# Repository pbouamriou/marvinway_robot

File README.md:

# marvinway
Source du projet Marvin Way (le segway depressif O_o)

## Arborescence ##

### brain ###

Projet de la carte de contrôle Haut niveau de Marvin

### control

Projet pour la carte de contrôle des moteurs

### docs

Contient la documentation globale du projet

### experience

Contient les exemples des expériences associés au projet marvinway

### meca

Contient la conception mecanique de Marvin

### shield

Projet permettant la communication entre le Brain et le reste du monde (la moelle epinière en soit)

### supply

Projet de gestion de l'alimentation

### utils

Contient des librairies utils ou des ensembles de configurations

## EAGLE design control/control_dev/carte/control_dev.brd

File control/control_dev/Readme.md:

# Carte de développement pour le pilotage des moteurs

## Configuration

Vous devez suivre la procédure de configuration d'EAGLE décrite dans le README situé dans utils/Eagle 

Pour ajouter le projet dans Eagle :

- Aller dans le `Control Panel -> Directories`

- Dans le cinquième champs `Projects` ajouter le répertoire correspondant au répertoire parent du répertoire carte

## Sources

[add custom project folder into eagle]: http://fsdportal.com/add-custom-project-folder-eagle-control-panel/	"add custom project folder into eagle"

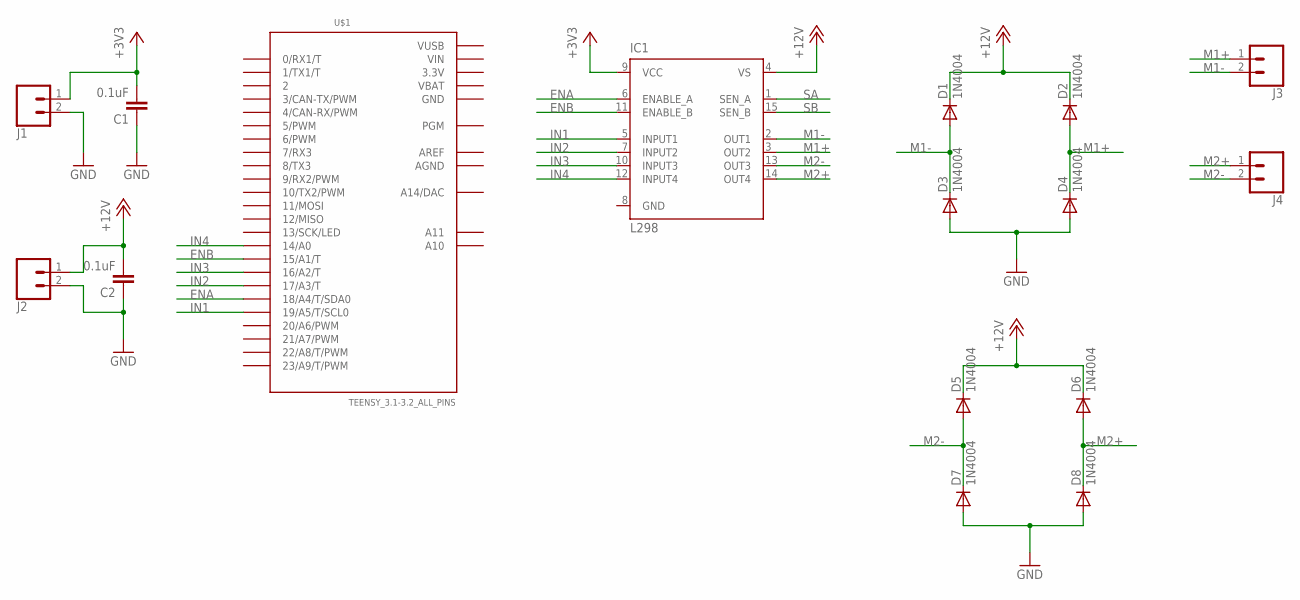
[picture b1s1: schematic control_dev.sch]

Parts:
C1, C2: 0.1uF; CAP-PTH-SMALL-KIT
D1, D2, D3, D4, D5, D6, D7, D8: 1N4004; DO41-10
IC1: L298; MULTIWATT-15
J1, J2, J3, J4: CONN_023.5MM; SCREWTERMINAL-3.5MM-2
U$1: TEENSY_3.1-3.2_ALL_PINS; TEENSY_3.0-3.2&LC_ALL_PINS

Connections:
3.3V: U$1.3.3V, U$1.3.3V1 (3.3V)
+3V3: C1.2, IC1.9 (VCC), J1.1
+12V: C2.2, D1.C, D2.C, D5.C, D6.C, IC1.4 (VS), J2.1
AGND: U$1.AGND
AREF: U$1.AREF
ENA: IC1.6 (ENABLE_A), U$1.18/A4 (18/A4/T/SDA0)
ENB: IC1.11 (ENABLE_B), U$1.15/A1 (15/A1/T)
GND: C1.1, C2.1, D3.A, D4.A, D7.A, D8.A, IC1.8 (GND), J1.2, J2.2, U$1.GND, U$1.GND1 (GND)
IN1: IC1.5 (INPUT1), U$1.19/A5 (19/A5/T/SCL0)
IN2: IC1.7 (INPUT2), U$1.17/A3 (17/A3/T)
IN3: IC1.10 (INPUT3), U$1.16/A2 (16/A2/T)
IN4: IC1.12 (INPUT4), U$1.14/A0
M1+: D2.A, D4.C, IC1.3 (OUT2), J3.1
M1-: D1.A, D3.C, IC1.2 (OUT1), J3.2
M2+: D6.A, D8.C, IC1.14 (OUT4), J4.1
M2-: D5.A, D7.C, IC1.13 (OUT3), J4.2
SA: IC1.1 (SEN_A)
SB: IC1.15 (SEN_B)
VBAT: U$1.VBAT
VIN: U$1.VIN
VUSB: U$1.VUSB

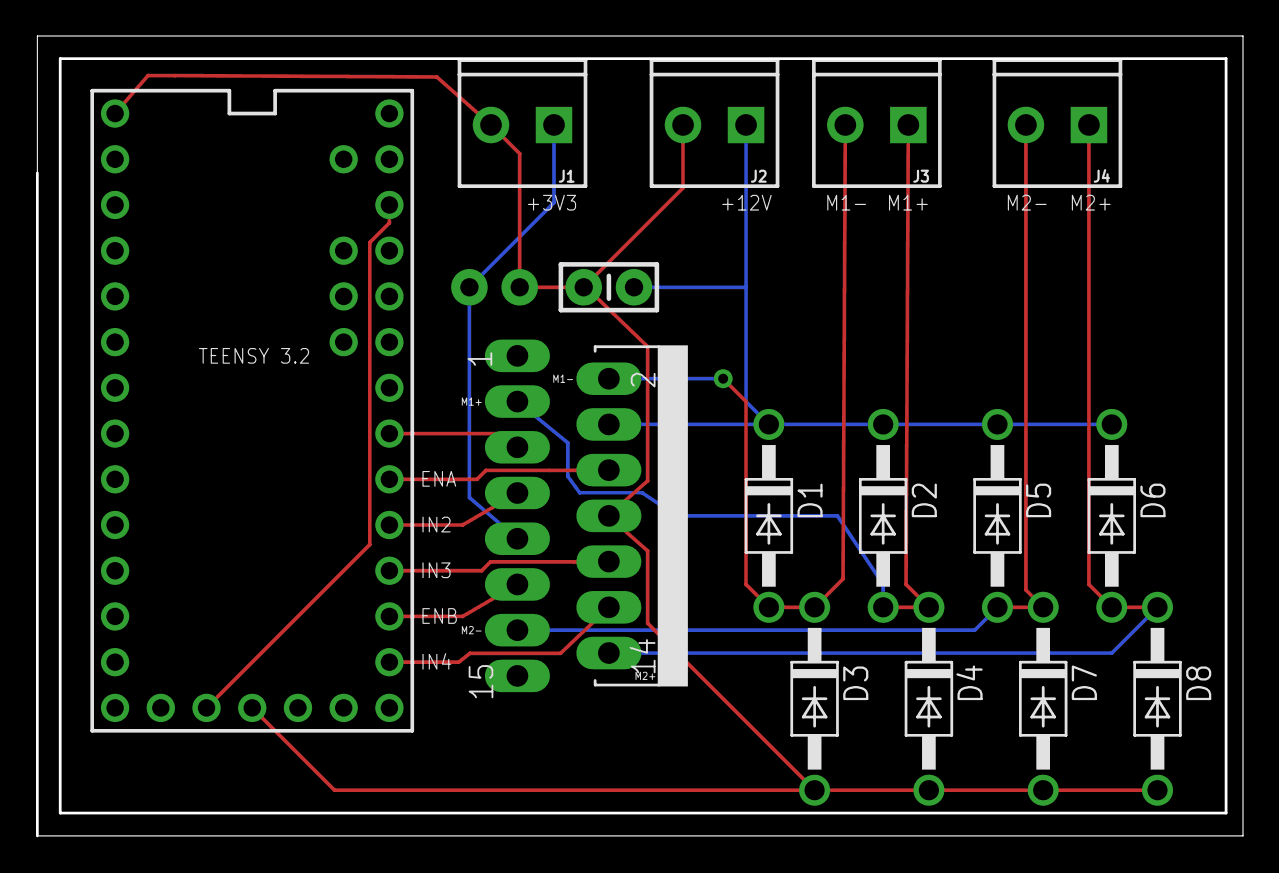
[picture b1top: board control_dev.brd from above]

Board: 2 copper layers, 66.9 x 44.4 mm, 16 parts (1 on the bottom side), 14 nets.

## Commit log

2016-01-30 ajout des pieces solidwors
2016-01-30 conception mecanique de marvin 1
2016-02-18 ajout de marvin
2016-02-22 ajout de la tete de marvin sous solidworks
2016-02-25 Ajout d'un programme de test qui est produit grace a CMAKE.
2016-02-25 Enrichissement du README.md pour ajouter des explications sur l'installation de l'environement.
2016-03-02 Ajout de nouveaux tests + correction cmake (upload et librairies).
2016-03-02 Maj de la documentation par rapport à cmake et l'upload.
2016-03-06 ajout du fichier tex décrivant les besoins de Marvin
2016-03-07 ajout du cours d'élec basé sur les vidéos de Thonain
2016-03-07 correction comprenant pour que les références vers la courbe se fassent correctement
2016-03-16 Ajout du programme de pilotage du potentiometre numerique.
2016-04-19 Ajout d'un test de pwm avec écran LCD.
2016-04-26 Ajout de CMake pour latex
2016-05-03 Ajout d'un programme qui augmente et diminue automatiquement une pwm sur la pin 3 de la teensy pour ajuster la vitesse du moteur sur un circuit de puissance
2016-05-03 Ajustement de Arduino.cmake pour qu'il utilise teensy_loader_cli au lieu de teensy pour déployer sur la teensy directement
2016-05-03 ajout du script d'installation teensy_loader_cli pour la compatibilité avec le nouveau build cmake
2016-05-03 Ajout d'un paragraphe de description pour installation de la commande teensy_loader_cli
2016-05-17 Ajout doc (partiel) sur le driver de mofset.
2016-05-17 Mise a jour de la documentation pour les transistors MOFSET
2016-05-17 Ajout d'une regle pour gitignore
2016-05-31 Ajout de quelques chapitre à compléter et mise à jour du CMake pour la gestion de bibtex
2016-07-06 Ajout d'un programme de visualisation gyroscopic OpenGL
2016-08-09 application OpenGL pour observer le comportement du capteur IMU5066
2016-08-09 Ajout d'une cheat sheet for vim
2016-08-09 Ajout des librairie d'utilisation du MPU6050 compilé avec cmake
2016-08-09 ajout du fichier bibtex pour la bibliographie
2016-08-09 renommage de setup en configure
2016-08-09 ajout du dépot de gestion des ports series
2016-08-09 mise à jour de configure
2016-08-09 Ajout du sous module pour les ports séries
2016-08-10 modification des valeurs offset initiales du gyroscrope Ajout d'un README.md pour utiliser le gyroscope Modification du dépot serial pour une integration plus facile
2016-08-10 Ajout du svg teensy
2016-08-10 Ajout du svg dans le markdown
2016-08-10 Correction ajout svg dans markdown
2016-08-10 correction README
2016-08-10 Tentative d'affichage d'une icone en png dans le markdown
2016-12-20 Mise en gconf de la partie vhdl
2016-12-20 Ajout de l'environement de test.
2016-12-20 Correctionde l'environement de simulation du decodeur
2017-01-16 Ajout du code vhdl qui fait la gestion memeoire des servomoteur + script
2017-01-31 Ajout du module servomoteur, avec l environement de simultation associé
2017-01-31 Ajout du dirvers avec des consignes en angle de 0 a 180 deg
2017-01-31 Ajout du module en charge des IO
2017-02-28 debug du module inputoutput
2017-03-28 Ajout de la datasheet du composant ADC sur 12bit, avec 8 channels
2017-05-01 Version initiale FPGA pour papilioone
2017-05-16 mise à jour de mpu6050
2017-05-16 Passage de test_pwm avec la nouvelle toolchains
2017-05-16 Portage de testServo
2017-05-16 Suppression du sous module serial
2017-05-16 passage de test_blink avec la nouvelle toolchain
2017-05-16 Mise à jour de la toolchain auto_pwm
2017-05-16 Modification de l'arborescence de MarvinWay
2017-05-16 Vrai push de l'arborescence
2017-05-23 Ajout du projet d'exemple pour teensy
2017-05-30 Ajout du sous projet MPU6050
2017-06-13 Ajout du petit projet d'exemple d'asservissement avec une petite machine à état
2017-10-25 Ajout du design de la carte de control de développement
2017-11-01 Ajout de la documentation concernant le pont en H
2018-02-23 réorganisation + doc + tests fpga (xilinx spartan6)

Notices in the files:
parts and their libraries:
SparkFun-Capacitors: Licensing: Creative Commons ShareAlike 4.0 International - https://creativecommons.org/licenses/by-sa/4.0
